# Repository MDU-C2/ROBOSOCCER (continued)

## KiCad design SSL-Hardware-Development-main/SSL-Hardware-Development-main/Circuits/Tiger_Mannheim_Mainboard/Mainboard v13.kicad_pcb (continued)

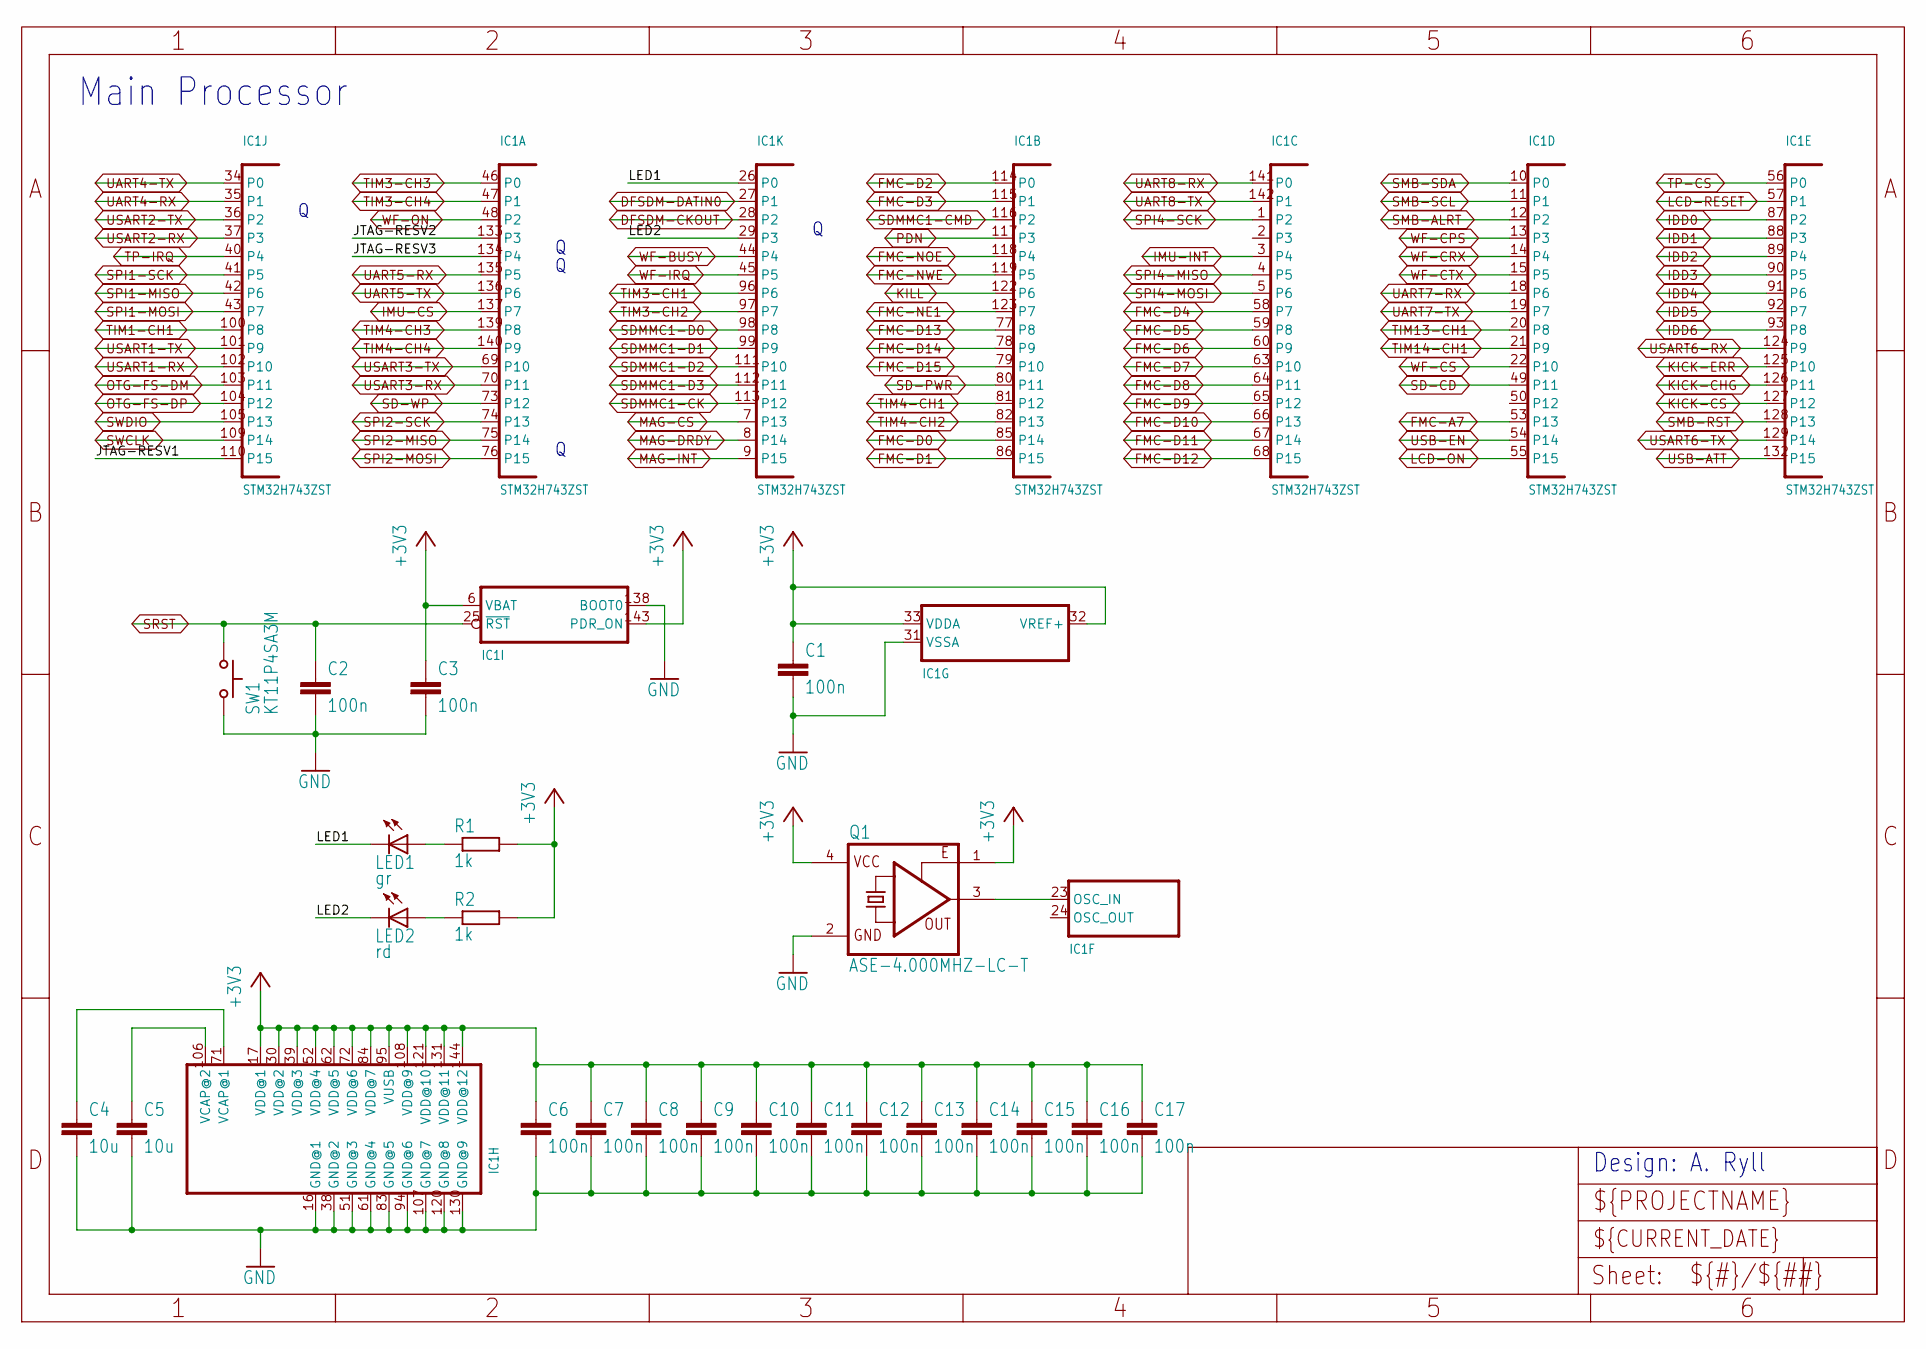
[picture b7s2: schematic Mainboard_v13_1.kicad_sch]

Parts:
C1, C2, C3, C6, C7, C8, C9, C10, C11, C12, C13, C14, C15, C16, C17: 100n; C0603
C4, C5: 10u; C0603
IC1: STM32H743ZST; LQFP144-ST
LED1: gr; CHIP-LED0603
LED2: rd; CHIP-LED0603
Q1: ASE-4.000MHZ-LC-T; OSCI-ASE
R1, R2: 1k; R0603
SW1: KT11P4SA3M; BUTTON4

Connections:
+3V3: C1.1, C3.1, C6.1, C7.1, C8.1, C9.1, C10.1, C11.1, C12.1, C13.1, C14.1, C15.1, C16.1, C17.1, IC1.6 (VBAT), IC1.17 (VDD@1), IC1.30 (VDD@2), IC1.32 (VREF+), IC1.33 (VDDA), IC1.39 (VDD@3), IC1.52 (VDD@4), IC1.62 (VDD@5), IC1.72 (VDD@6), IC1.84 (VDD@7), IC1.95 (VUSB), IC1.108 (VDD@9), IC1.121 (VDD@10), IC1.131 (VDD@11), IC1.143 (PDR_ON), IC1.144 (VDD@12), Q1.1 (OE), Q1.4 (VCC), R1.2, R2.2; also elsewhere on the board
DFSDM-CKOUT: IC1.28 (P2); also elsewhere on the board
DFSDM-DATIN0: IC1.27 (P1); also elsewhere on the board
FMC-A7: IC1.53 (P13); also elsewhere on the board
FMC-D0: IC1.85 (P14); also elsewhere on the board
FMC-D1: IC1.86 (P15); also elsewhere on the board
FMC-D2: IC1.114 (P0); also elsewhere on the board
FMC-D3: IC1.115 (P1); also elsewhere on the board
FMC-D4: IC1.58 (P7); also elsewhere on the board
FMC-D5: IC1.59 (P8); also elsewhere on the board
FMC-D6: IC1.60 (P9); also elsewhere on the board
FMC-D7: IC1.63 (P10); also elsewhere on the board
FMC-D8: IC1.64 (P11); also elsewhere on the board
FMC-D9: IC1.65 (P12); also elsewhere on the board
FMC-D10: IC1.66 (P13); also elsewhere on the board
FMC-D11: IC1.67 (P14); also elsewhere on the board
FMC-D12: IC1.68 (P15); also elsewhere on the board
FMC-D13: IC1.77 (P8); also elsewhere on the board
FMC-D14: IC1.78 (P9); also elsewhere on the board
FMC-D15: IC1.79 (P10); also elsewhere on the board
FMC-NE1: IC1.123 (P7); also elsewhere on the board
FMC-NOE: IC1.118 (P4); also elsewhere on the board
FMC-NWE: IC1.119 (P5); also elsewhere on the board
GND: C1.2, C2.2, C3.2, C4.2, C5.2, C6.2, C7.2, C8.2, C9.2, C10.2, C11.2, C12.2, C13.2, C14.2, C15.2, C16.2, C17.2, IC1.16 (GND@1), IC1.31 (VSSA), IC1.38 (GND@2), IC1.51 (GND@3), IC1.61 (GND@4), IC1.83 (GND@5), IC1.94 (GND@6), IC1.107 (GND@7), IC1.120 (GND@8), IC1.130 (GND@9), IC1.138 (BOOT0), Q1.2 (GND), SW1.3 (2), SW1.4 (2); also elsewhere on the board
IDD0: IC1.87 (P2); also elsewhere on the board
IDD1: IC1.88 (P3); also elsewhere on the board
IDD2: IC1.89 (P4); also elsewhere on the board
IDD3: IC1.90 (P5); also elsewhere on the board
IDD4: IC1.91 (P6); also elsewhere on the board
IDD5: IC1.92 (P7); also elsewhere on the board
IDD6: IC1.93 (P8); also elsewhere on the board
IMU-CS: IC1.137 (P7); also elsewhere on the board
IMU-INT: IC1.3 (P4); also elsewhere on the board
JTAG-RESV1: IC1.110 (P15)
JTAG-RESV2: IC1.133 (P3)
JTAG-RESV3: IC1.134 (P4)
KICK-CHG: IC1.126 (P11); also elsewhere on the board
KICK-CS: IC1.127 (P12); also elsewhere on the board
KICK-ERR: IC1.125 (P10); also elsewhere on the board
KILL: IC1.122 (P6); also elsewhere on the board
LCD-ON: IC1.55 (P15); also elsewhere on the board
LCD-RESET: IC1.57 (P1); also elsewhere on the board
LED1: IC1.26 (P0), LED1.C
LED2: IC1.29 (P3), LED2.C
MAG-CS: IC1.7 (P13); also elsewhere on the board
MAG-DRDY: IC1.8 (P14); also elsewhere on the board
MAG-INT: IC1.9 (P15); also elsewhere on the board
unnamed: LED1.A, R1.1
unnamed: LED2.A, R2.1
unnamed: IC1.23 (OSC_IN), Q1.3 (FO)
unnamed: C5.1, IC1.106 (VCAP@2)
unnamed: C4.1, IC1.71 (VCAP@1)
OTG-FS-DM: IC1.103 (P11); also elsewhere on the board
OTG-FS-DP: IC1.104 (P12); also elsewhere on the board
PDN: IC1.117 (P3); also elsewhere on the board
SD-CD: IC1.49 (P11); also elsewhere on the board
SD-PWR: IC1.80 (P11); also elsewhere on the board
SD-WP: IC1.73 (P12); also elsewhere on the board
SDMMC1-CK: IC1.113 (P12); also elsewhere on the board
SDMMC1-CMD: IC1.116 (P2); also elsewhere on the board
SDMMC1-D0: IC1.98 (P8); also elsewhere on the board
SDMMC1-D1: IC1.99 (P9); also elsewhere on the board
SDMMC1-D2: IC1.111 (P10); also elsewhere on the board
SDMMC1-D3: IC1.112 (P11); also elsewhere on the board
SMB-ALRT: IC1.12 (P2); also elsewhere on the board
SMB-RST: IC1.128 (P13); also elsewhere on the board
SMB-SCL: IC1.11 (P1); also elsewhere on the board
SMB-SDA: IC1.10 (P0); also elsewhere on the board
SPI1-MISO: IC1.42 (P6); also elsewhere on the board
SPI1-MOSI: IC1.43 (P7); also elsewhere on the board
SPI1-SCK: IC1.41 (P5); also elsewhere on the board
SPI2-MISO: IC1.75 (P14); also elsewhere on the board
SPI2-MOSI: IC1.76 (P15); also elsewhere on the board
SPI2-SCK: IC1.74 (P13); also elsewhere on the board
SPI4-MISO: IC1.4 (P5); also elsewhere on the board
SPI4-MOSI: IC1.5 (P6); also elsewhere on the board
SPI4-SCK: IC1.1 (P2); also elsewhere on the board
SRST: C2.1, IC1.25 (~RST), SW1.1, SW1.2 (1); also elsewhere on the board
SWCLK: IC1.109 (P14); also elsewhere on the board
SWDIO: IC1.105 (P13); also elsewhere on the board
TIM1-CH1: IC1.100 (P8); also elsewhere on the board
TIM3-CH1: IC1.96 (P6); also elsewhere on the board
TIM3-CH2: IC1.97 (P7); also elsewhere on the board
TIM3-CH3: IC1.46 (P0); also elsewhere on the board
TIM3-CH4: IC1.47 (P1); also elsewhere on the board
TIM4-CH1: IC1.81 (P12); also elsewhere on the board
TIM4-CH2: IC1.82 (P13); also elsewhere on the board
TIM4-CH3: IC1.139 (P8); also elsewhere on the board
TIM4-CH4: IC1.140 (P9); also elsewhere on the board
TIM13-CH1: IC1.20 (P8); also elsewhere on the board
TIM14-CH1: IC1.21 (P9); also elsewhere on the board
TP-CS: IC1.56 (P0); also elsewhere on the board
TP-IRQ: IC1.40 (P4); also elsewhere on the board
UART4-RX: IC1.35 (P1); also elsewhere on the board
UART4-TX: IC1.34 (P0); also elsewhere on the board
UART5-RX: IC1.135 (P5); also elsewhere on the board
UART5-TX: IC1.136 (P6); also elsewhere on the board
UART7-RX: IC1.18 (P6); also elsewhere on the board
UART7-TX: IC1.19 (P7); also elsewhere on the board
UART8-RX: IC1.141 (P0); also elsewhere on the board
UART8-TX: IC1.142 (P1); also elsewhere on the board
USART1-RX: IC1.102 (P10); also elsewhere on the board
USART1-TX: IC1.101 (P9); also elsewhere on the board
USART2-RX: IC1.37 (P3); also elsewhere on the board
USART2-TX: IC1.36 (P2); also elsewhere on the board
USART3-RX: IC1.70 (P11); also elsewhere on the board
USART3-TX: IC1.69 (P10); also elsewhere on the board
USART6-RX: IC1.124 (P9); also elsewhere on the board
USART6-TX: IC1.129 (P14); also elsewhere on the board
USB-ATT: IC1.132 (P15); also elsewhere on the board
USB-EN: IC1.54 (P14); also elsewhere on the board
WF-BUSY: IC1.44 (P4); also elsewhere on the board
WF-CPS: IC1.13 (P3); also elsewhere on the board
WF-CRX: IC1.14 (P4); also elsewhere on the board
WF-CS: IC1.22 (P10); also elsewhere on the board
WF-CTX: IC1.15 (P5); also elsewhere on the board
WF-IRQ: IC1.45 (P5); also elsewhere on the board
WF-ON: IC1.48 (P2); also elsewhere on the board

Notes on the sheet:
Main Processor
Design: A. Ryll

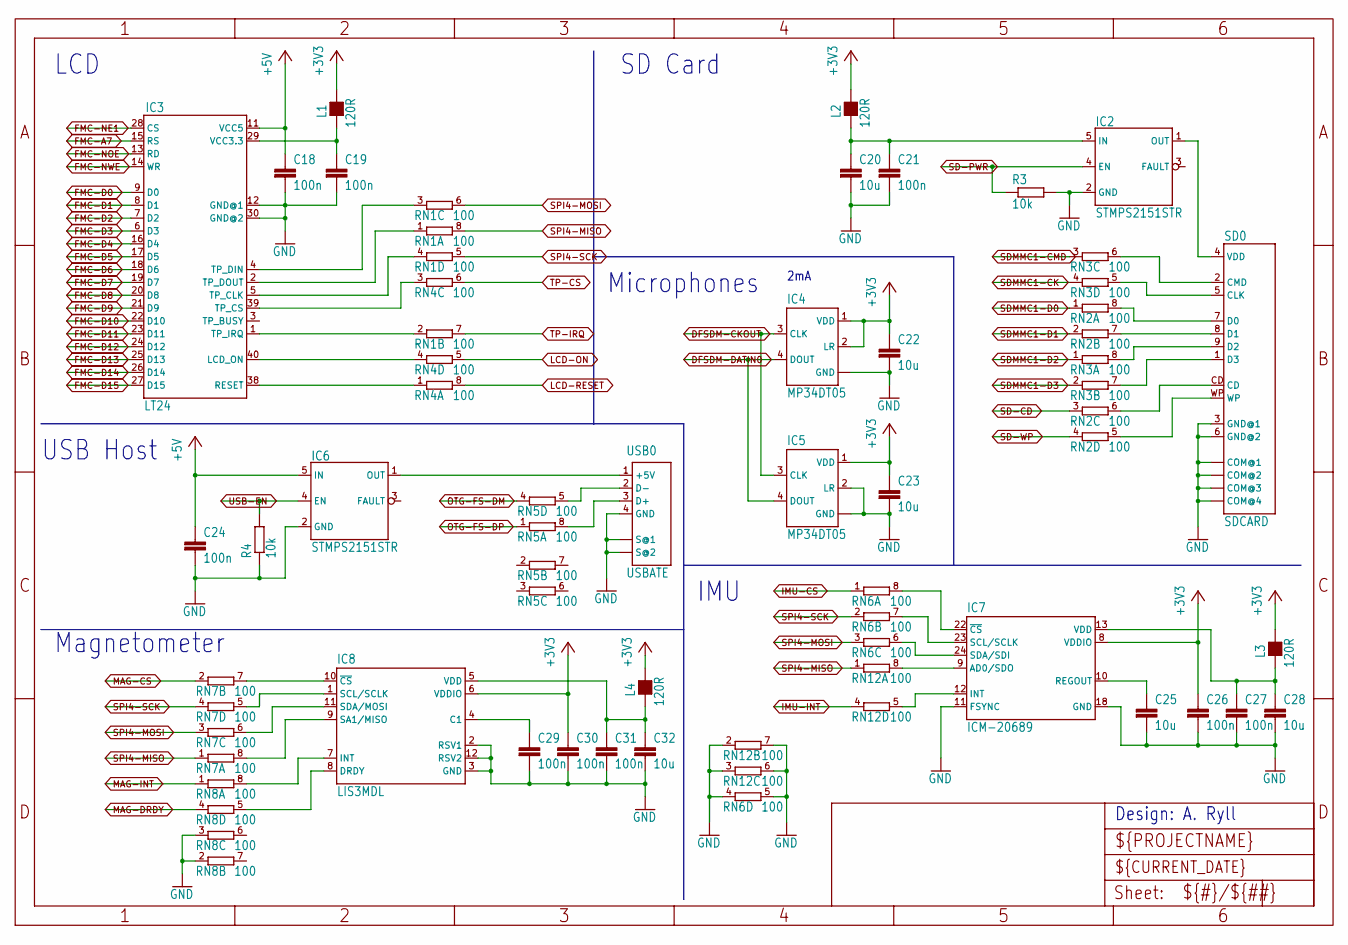
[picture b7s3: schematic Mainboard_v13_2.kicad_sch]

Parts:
C18, C19, C21, C24, C26, C27, C29, C30, C31: 100n; C0603
C20, C22, C23, C25, C28, C32: 10u; C0603
IC2, IC6: STMPS2151STR; SOT23-5
IC3: LT24
IC4, IC5: MP34DT05; HCLGA4
IC7: ICM-20689; QFN24-4X4-P
IC8: LIS3MDL; VFLGA-12
L1, L2, L3, L4: 120R; L0603
R3, R4: 10k; R0603
RN1, RN2, RN3, RN4, RN5, RN6, RN7, RN8, RN12: 100; EXB28V
SD0: SDCARD
USB0: USBATE; USBA-TE

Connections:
+3V3: C22.1, C23.1, C26.1, C30.1, IC4.1 (VDD), IC4.2 (LR), IC5.1 (VDD), IC7.8 (VDDIO), IC8.6 (VDDIO), L1.2, L2.2, L3.2, L4.2; also elsewhere on the board
+5V: C18.1, C24.1, IC3.11 (VCC5), IC6.5 (IN); also elsewhere on the board
DFSDM-CKOUT: IC4.3 (CLK), IC5.3 (CLK); also elsewhere on the board
DFSDM-DATIN0: IC4.4 (DOUT), IC5.4 (DOUT); also elsewhere on the board
FMC-A7: IC3.15 (RS); also elsewhere on the board
FMC-D0: IC3.9 (D0); also elsewhere on the board
FMC-D1: IC3.8 (D1); also elsewhere on the board
FMC-D2: IC3.7 (D2); also elsewhere on the board
FMC-D3: IC3.6 (D3); also elsewhere on the board
FMC-D4: IC3.16 (D4); also elsewhere on the board
FMC-D5: IC3.17 (D5); also elsewhere on the board
FMC-D6: IC3.18 (D6); also elsewhere on the board
FMC-D7: IC3.19 (D7); also elsewhere on the board
FMC-D8: IC3.20 (D8); also elsewhere on the board
FMC-D9: IC3.21 (D9); also elsewhere on the board
FMC-D10: IC3.22 (D10); also elsewhere on the board
FMC-D11: IC3.23 (D11); also elsewhere on the board
FMC-D12: IC3.24 (D12); also elsewhere on the board
FMC-D13: IC3.25 (D13); also elsewhere on the board
FMC-D14: IC3.26 (D14); also elsewhere on the board
FMC-D15: IC3.27 (D15); also elsewhere on the board
FMC-NE1: IC3.28 (CS); also elsewhere on the board
FMC-NOE: IC3.13 (RD); also elsewhere on the board
FMC-NWE: IC3.14 (WR); also elsewhere on the board
GND: C18.2, C19.2, C20.2, C21.2, C22.2, C23.2, C24.2, C25.2, C26.2, C27.2, C28.2, C29.2, C30.2, C31.2, C32.2, IC2.2 (GND), IC3.12 (GND@1), IC3.30 (GND@2), IC4.G1 (GND), IC4.G2 (GND), IC4.G3 (GND), IC4.G4 (GND), IC5.2 (LR), IC5.G1 (GND), IC5.G2 (GND), IC5.G3 (GND), IC5.G4 (GND), IC6.2 (GND), IC7.11 (FSYNC), IC7.18 (GND), IC8.2 (RSV1), IC8.3 (GND), IC8.12 (RSV2), R3.2, R4.1, RN6.4 (1), RN6.5 (2), RN8.2 (1), RN8.3 (1), RN12.2 (1), RN12.3 (1), RN12.6 (2), RN12.7 (2), SD0.3 (GND@1), SD0.6 (GND@2), SD0.COM1 (COM@1), SD0.COM2 (COM@2), SD0.COM3 (COM@3), SD0.COM4 (COM@4), USB0.4 (GND), USB0.MNT1 (S@1), USB0.MNT2 (S@2); also elsewhere on the board
IMU-CS: RN6.1; also elsewhere on the board
IMU-INT: RN12.4 (1); also elsewhere on the board
LCD-ON: RN4.5 (2); also elsewhere on the board
LCD-RESET: RN4.8 (2); also elsewhere on the board
MAG-CS: RN7.2 (1); also elsewhere on the board
MAG-DRDY: RN8.4 (1); also elsewhere on the board
MAG-INT: RN8.1; also elsewhere on the board
unnamed: IC8.10 (~CS), RN7.7 (2)
unnamed: IC8.1 (SCL/SCLK), RN7.5 (2)
unnamed: IC8.11 (SDA/MOSI), RN7.6 (2)
unnamed: IC8.9 (SA1/MISO), RN7.8 (2)
unnamed: IC8.7 (INT), RN8.8 (2)
unnamed: IC8.8 (DRDY), RN8.5 (2)
unnamed: C29.1, IC8.4 (C1)
unnamed: C31.1, C32.1, IC8.5 (VDD), L4.1
unnamed: IC7.12 (INT), RN12.5 (2)
unnamed: C19.1, IC3.29 (VCC3.3), L1.1
unnamed: IC3.38 (RESET), RN4.1
unnamed: IC3.40 (LCD_ON), RN4.4 (1)
unnamed: IC3.1 (TP_IRQ), RN1.2 (1)
unnamed: IC3.39 (TP_CS), RN4.3 (1)
unnamed: IC3.5 (TP_CLK), RN1.4 (1)
unnamed: IC3.2 (TP_DOUT), RN1.1
unnamed: IC3.4 (TP_DIN), RN1.3 (1)
unnamed: RN2.7 (2), SD0.8 (D1)
unnamed: RN2.8 (2), SD0.7 (D0)
unnamed: RN3.5 (2), SD0.5 (CLK)
unnamed: RN3.6 (2), SD0.2 (CMD)
unnamed: RN3.8 (2), SD0.9 (D2)
unnamed: RN3.7 (2), SD0.1 (D3)
unnamed: RN2.6 (2), SD0.CD
unnamed: RN2.5 (2), SD0.WP
unnamed: C20.1, C21.1, IC2.5 (IN), L2.1
unnamed: IC6.1 (OUT), USB0.1 (+5V)
unnamed: RN5.5 (2), USB0.2 (D-)
unnamed: RN5.8 (2), USB0.3 (D+)
unnamed: IC7.9 (AD0/SDO), RN12.8 (2)
unnamed: C25.1, IC7.10 (REGOUT)
unnamed: C27.1, C28.1, IC7.13 (VDD), L3.1
unnamed: IC7.24 (SDA/SDI), RN6.6 (2)
unnamed: IC7.23 (SCL/SCLK), RN6.7 (2)
unnamed: IC7.22 (~CS), RN6.8 (2)
OTG-FS-DM: RN5.4 (1); also elsewhere on the board
OTG-FS-DP: RN5.1; also elsewhere on the board
SD-CD: RN2.3 (1); also elsewhere on the board
SD-PWR: IC2.4 (EN), R3.1; also elsewhere on the board
SD-WP: RN2.4 (1); also elsewhere on the board
SDMMC1-CK: RN3.4 (1); also elsewhere on the board
SDMMC1-CMD: RN3.3 (1); also elsewhere on the board
SDMMC1-D0: RN2.1; also elsewhere on the board
SDMMC1-D1: RN2.2 (1); also elsewhere on the board
SDMMC1-D2: RN3.1; also elsewhere on the board
SDMMC1-D3: RN3.2 (1); also elsewhere on the board
SD_PWR: IC2.1 (OUT), SD0.4 (VDD)
SPI4-MISO: RN1.8 (2), RN7.1, RN12.1; also elsewhere on the board
SPI4-MOSI: RN1.6 (2), RN6.3 (1), RN7.3 (1); also elsewhere on the board
SPI4-SCK: RN1.5 (2), RN6.2 (1), RN7.4 (1); also elsewhere on the board
TP-CS: RN4.6 (2); also elsewhere on the board
TP-IRQ: RN1.7 (2); also elsewhere on the board
USB-EN: IC6.4 (EN), R4.2; also elsewhere on the board

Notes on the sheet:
2mA
IMU
Design: A. Ryll
USB Host
SD Card
Magnetometer
Microphones
LCD

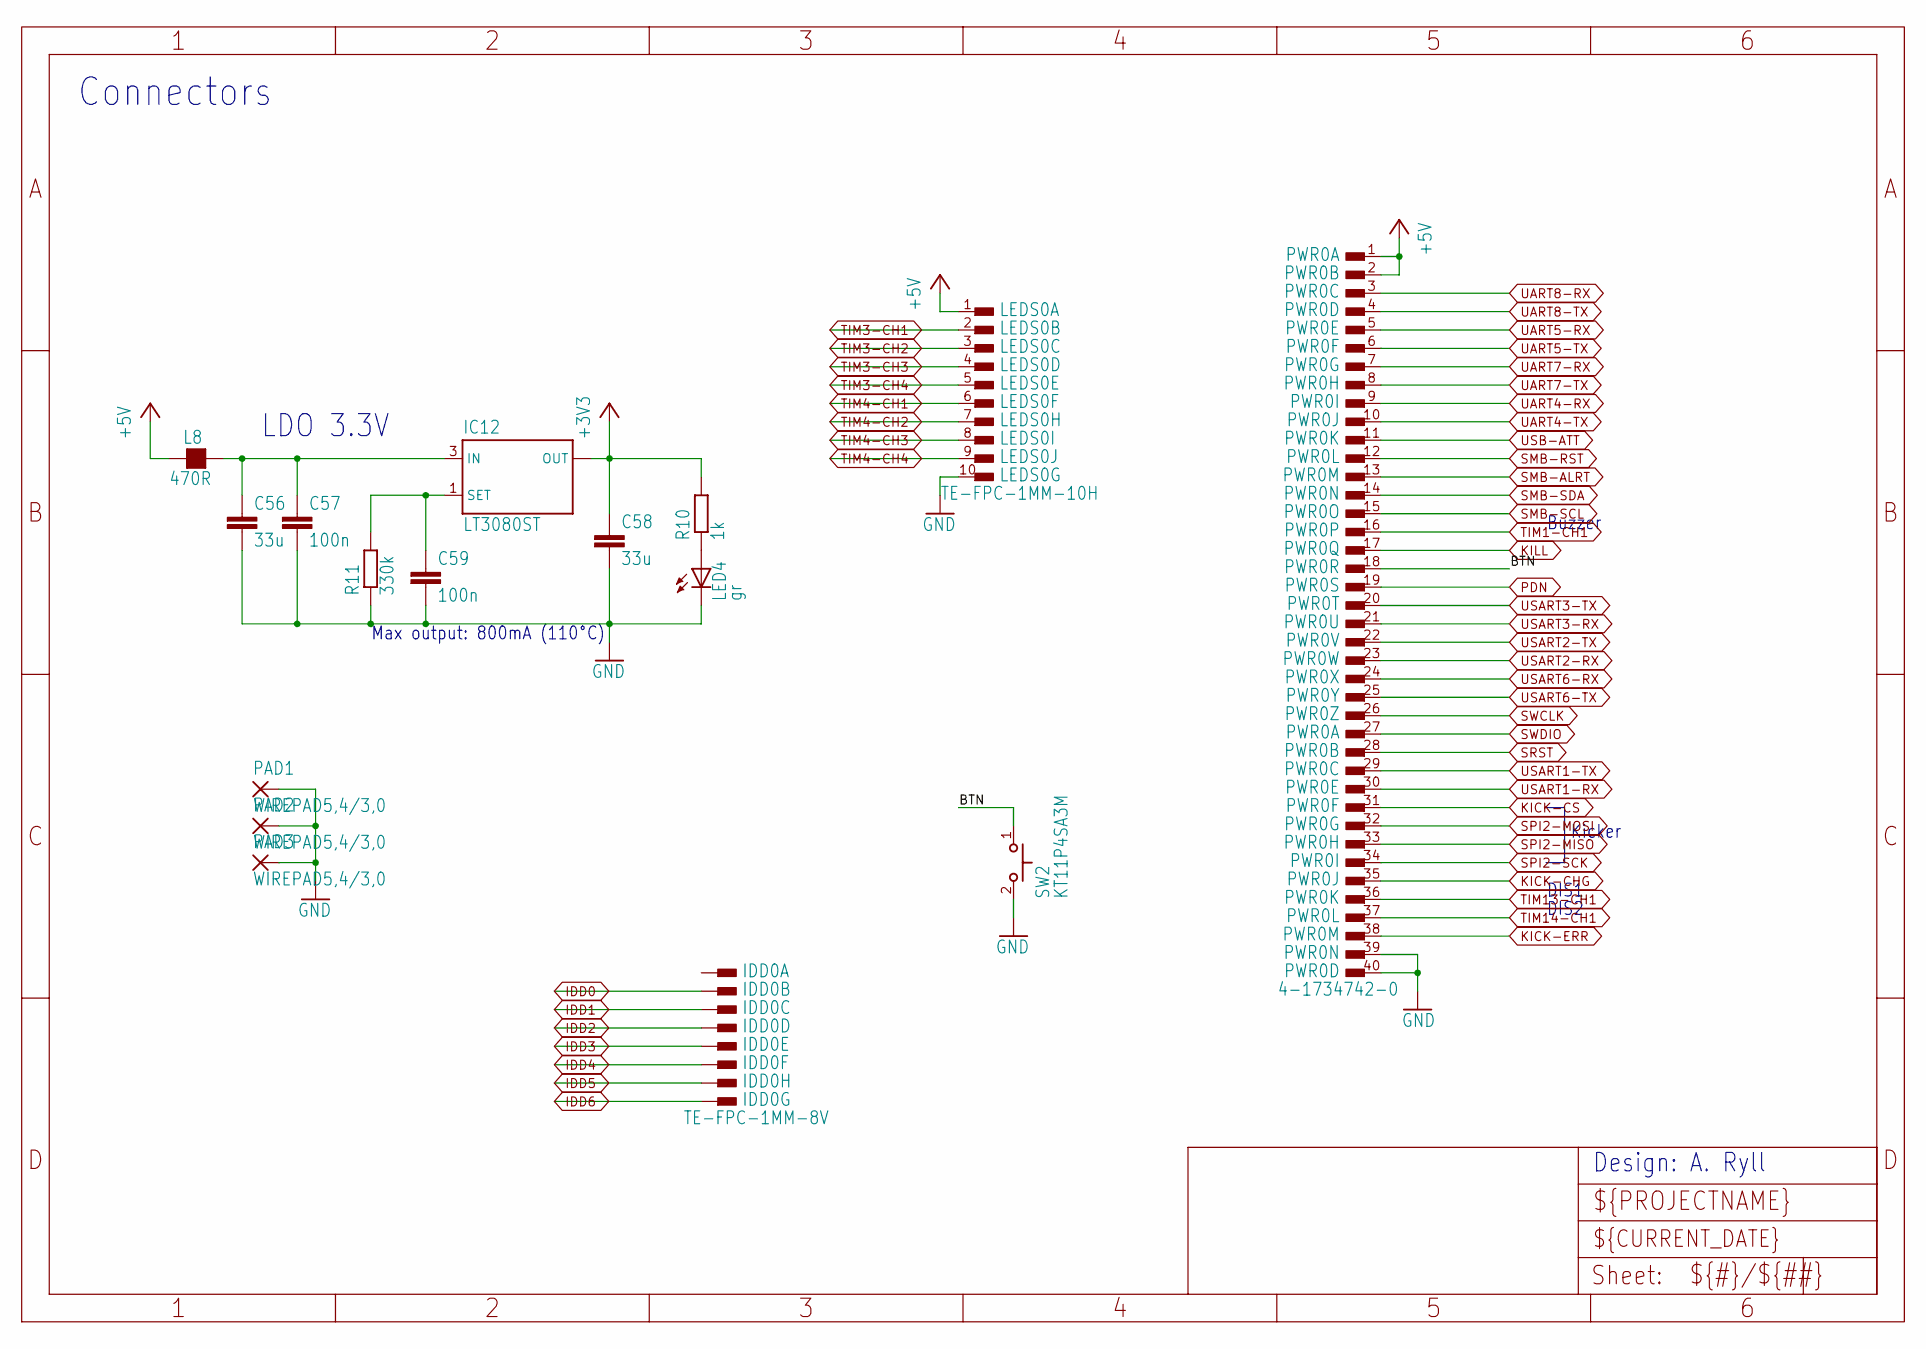
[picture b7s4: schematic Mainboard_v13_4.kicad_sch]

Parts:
C56, C58: 33u; C1206; VOLTAGE 25V
C57, C59: 100n; C0603
IC12: LT3080ST; SOT223
IDD0: TE-FPC-1MM-8V; TE-1734248-8
L8: 470R; L1206
LED4: gr; CHIP-LED0603
LEDS0: TE-FPC-1MM-10H; TE-1-84952-0
PAD1, PAD2, PAD3: WIREPAD5,4/3,0; 5,4_3,0
PWR0: 4-1734742-0; TE-4-1734592-0
R10: 1k; R0603
R11: 330k; R0603
SW2: KT11P4SA3M; KT11

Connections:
+3V3: C58.1, IC12.2 (OUT), IC12.4 (OUT), R10.2; also elsewhere on the board
+5V: L8.1, LEDS0.1, PWR0.1, PWR0.2; also elsewhere on the board
BTN: PWR0.18, SW2.1
GND: C56.2, C57.2, C58.2, C59.2, LED4.C, LEDS0.10, PAD1.1, PAD1.2, PAD2.1, PAD2.2, PAD3.1, PAD3.2, PWR0.39, PWR0.40, R11.1, SW2.2; also elsewhere on the board
IDD0: IDD0.A2, IDD0.B2; also elsewhere on the board
IDD1: IDD0.A3, IDD0.B3; also elsewhere on the board
IDD2: IDD0.A4, IDD0.B4; also elsewhere on the board
IDD3: IDD0.A5, IDD0.B5; also elsewhere on the board
IDD4: IDD0.A6, IDD0.B6; also elsewhere on the board
IDD5: IDD0.A7, IDD0.B7; also elsewhere on the board
IDD6: IDD0.A8, IDD0.B8; also elsewhere on the board
KICK-CHG: PWR0.35; also elsewhere on the board
KICK-CS: PWR0.31; also elsewhere on the board
KICK-ERR: PWR0.38; also elsewhere on the board
KILL: PWR0.17; also elsewhere on the board
unnamed: C59.1, IC12.1 (SET), R11.2
unnamed: LED4.A, R10.1
unnamed: C56.1, C57.1, IC12.3 (IN), L8.2
PDN: PWR0.19; also elsewhere on the board
SMB-ALRT: PWR0.13; also elsewhere on the board
SMB-RST: PWR0.12; also elsewhere on the board
SMB-SCL: PWR0.15; also elsewhere on the board
SMB-SDA: PWR0.14; also elsewhere on the board
SPI2-MISO: PWR0.33; also elsewhere on the board
SPI2-MOSI: PWR0.32; also elsewhere on the board
SPI2-SCK: PWR0.34; also elsewhere on the board
SRST: PWR0.28; also elsewhere on the board
SWCLK: PWR0.26; also elsewhere on the board
SWDIO: PWR0.27; also elsewhere on the board
TIM1-CH1: PWR0.16; also elsewhere on the board
TIM3-CH1: LEDS0.2; also elsewhere on the board
TIM3-CH2: LEDS0.3; also elsewhere on the board
TIM3-CH3: LEDS0.4; also elsewhere on the board
TIM3-CH4: LEDS0.5; also elsewhere on the board
TIM4-CH1: LEDS0.6; also elsewhere on the board
TIM4-CH2: LEDS0.7; also elsewhere on the board
TIM4-CH3: LEDS0.8; also elsewhere on the board
TIM4-CH4: LEDS0.9; also elsewhere on the board
TIM13-CH1: PWR0.36; also elsewhere on the board
TIM14-CH1: PWR0.37; also elsewhere on the board
UART4-RX: PWR0.9; also elsewhere on the board
UART4-TX: PWR0.10; also elsewhere on the board
UART5-RX: PWR0.5; also elsewhere on the board
UART5-TX: PWR0.6; also elsewhere on the board
UART7-RX: PWR0.7; also elsewhere on the board
UART7-TX: PWR0.8; also elsewhere on the board
UART8-RX: PWR0.3; also elsewhere on the board
UART8-TX: PWR0.4; also elsewhere on the board
USART1-RX: PWR0.30; also elsewhere on the board
USART1-TX: PWR0.29; also elsewhere on the board
USART2-RX: PWR0.23; also elsewhere on the board
USART2-TX: PWR0.22; also elsewhere on the board
USART3-RX: PWR0.21; also elsewhere on the board
USART3-TX: PWR0.20; also elsewhere on the board
USART6-RX: PWR0.24; also elsewhere on the board
USART6-TX: PWR0.25; also elsewhere on the board
USB-ATT: PWR0.11; also elsewhere on the board

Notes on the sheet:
Max output: 800mA (110°C)
LDO 3.3V
Connectors
Kicker
DIS1
DIS2
Design: A. Ryll
Buzzer

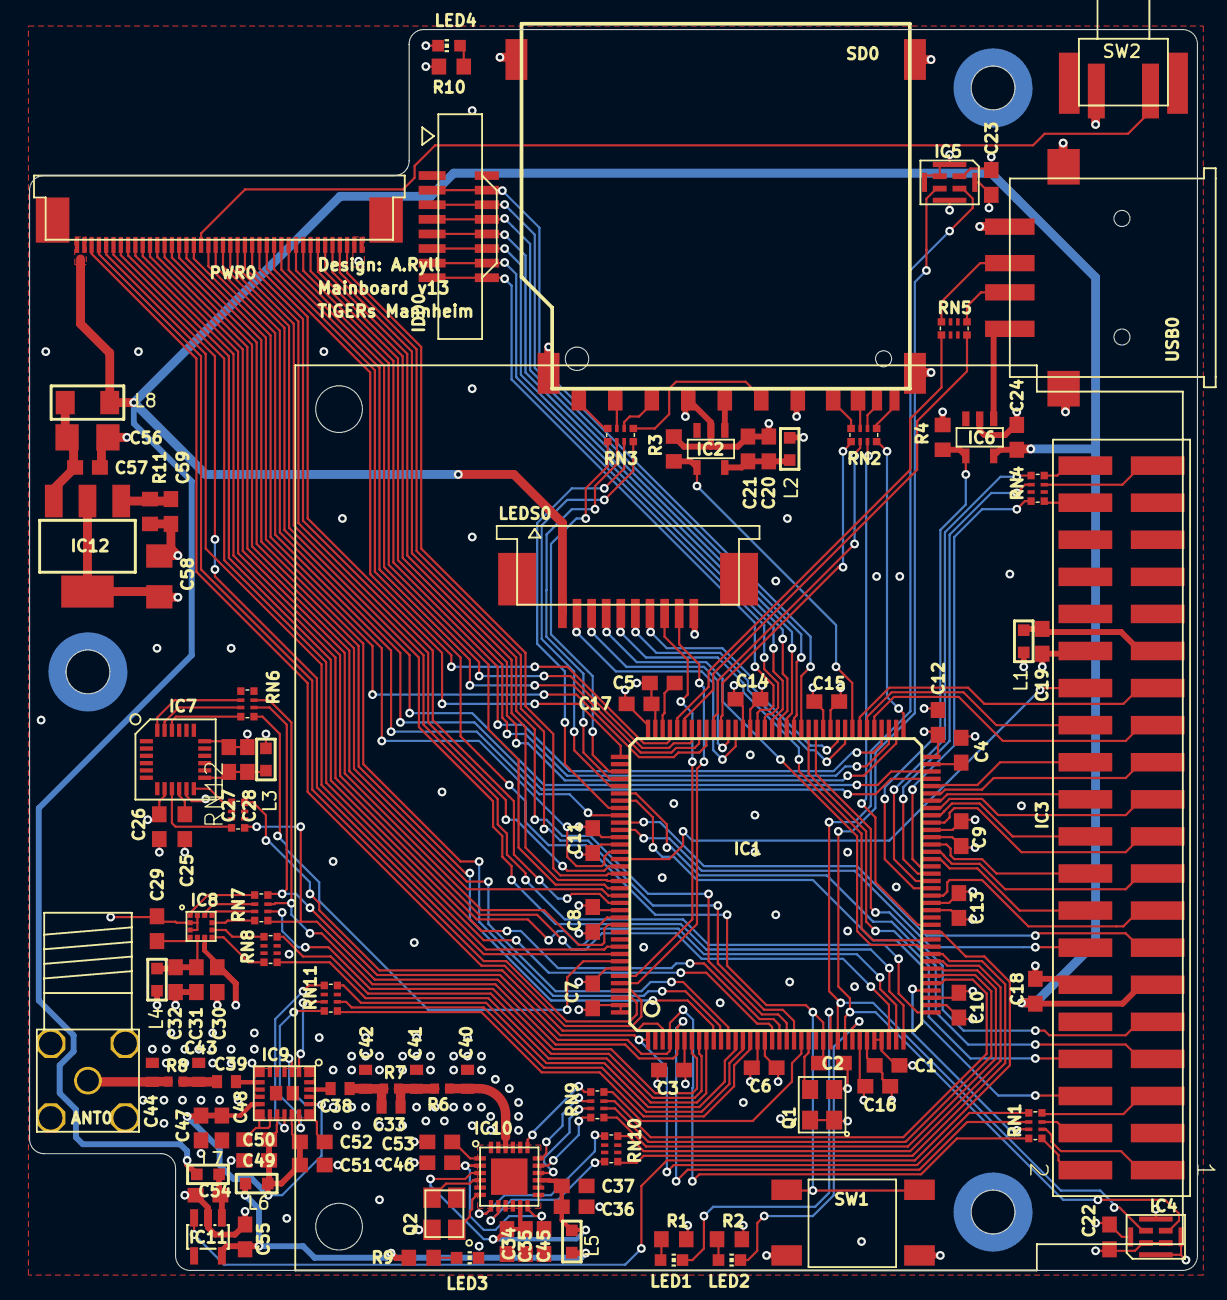
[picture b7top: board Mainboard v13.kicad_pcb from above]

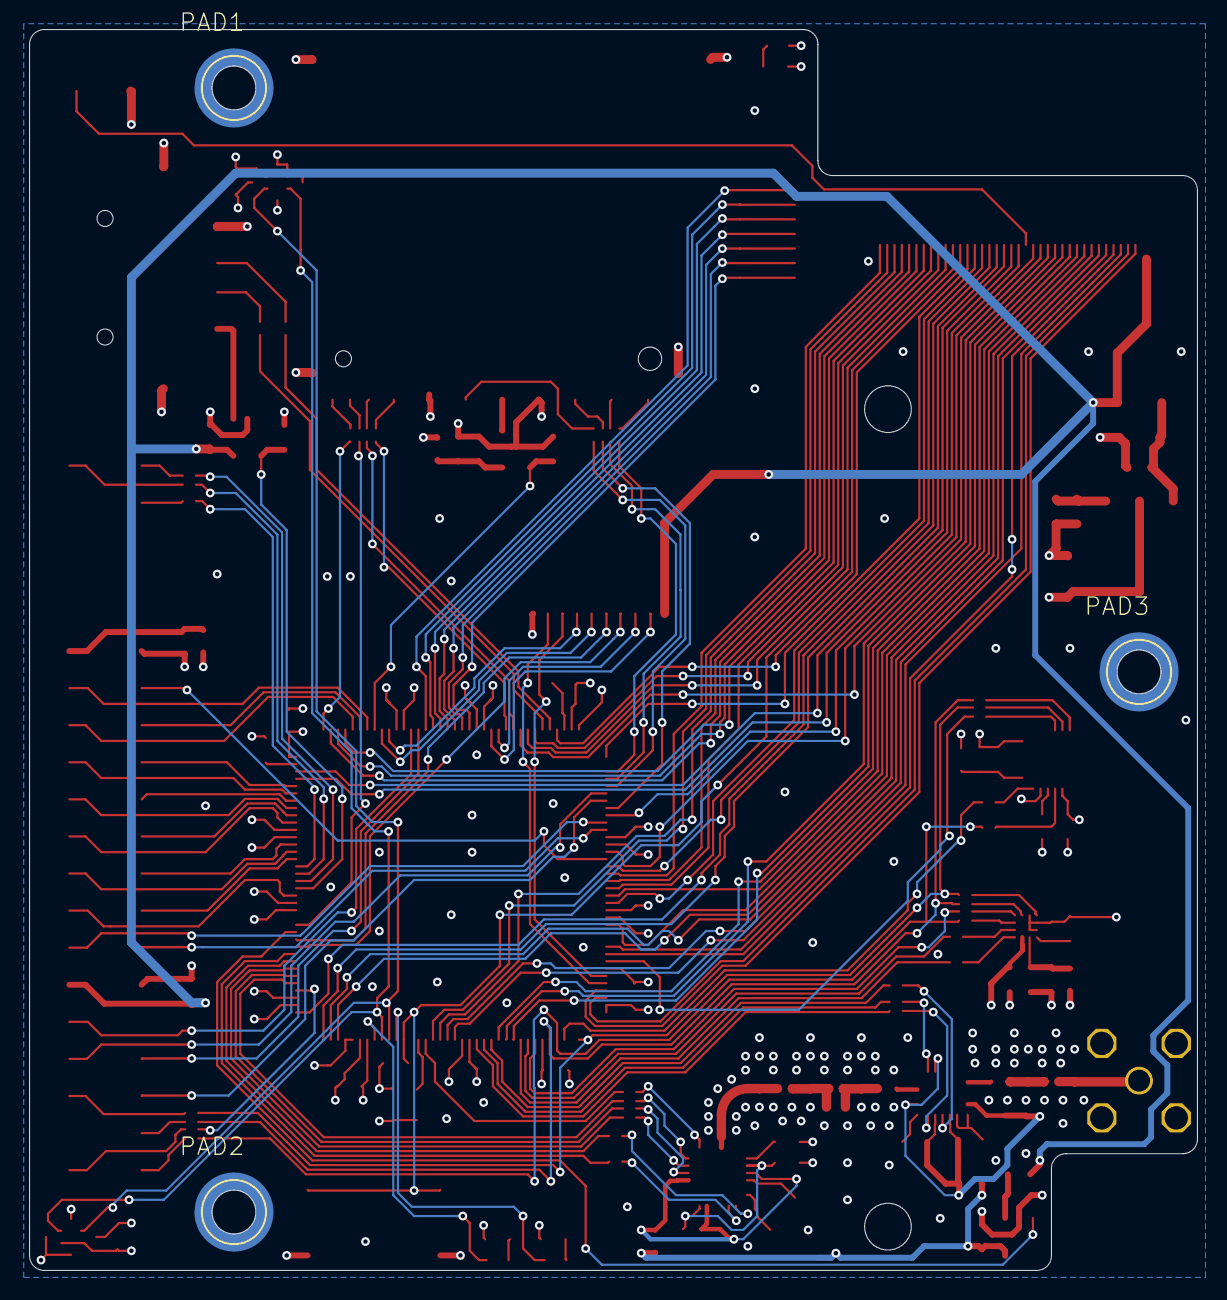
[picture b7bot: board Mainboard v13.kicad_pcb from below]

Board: 4 copper layers, 80.0 x 85.0 mm, 118 parts (3 on the bottom side), 181 nets.

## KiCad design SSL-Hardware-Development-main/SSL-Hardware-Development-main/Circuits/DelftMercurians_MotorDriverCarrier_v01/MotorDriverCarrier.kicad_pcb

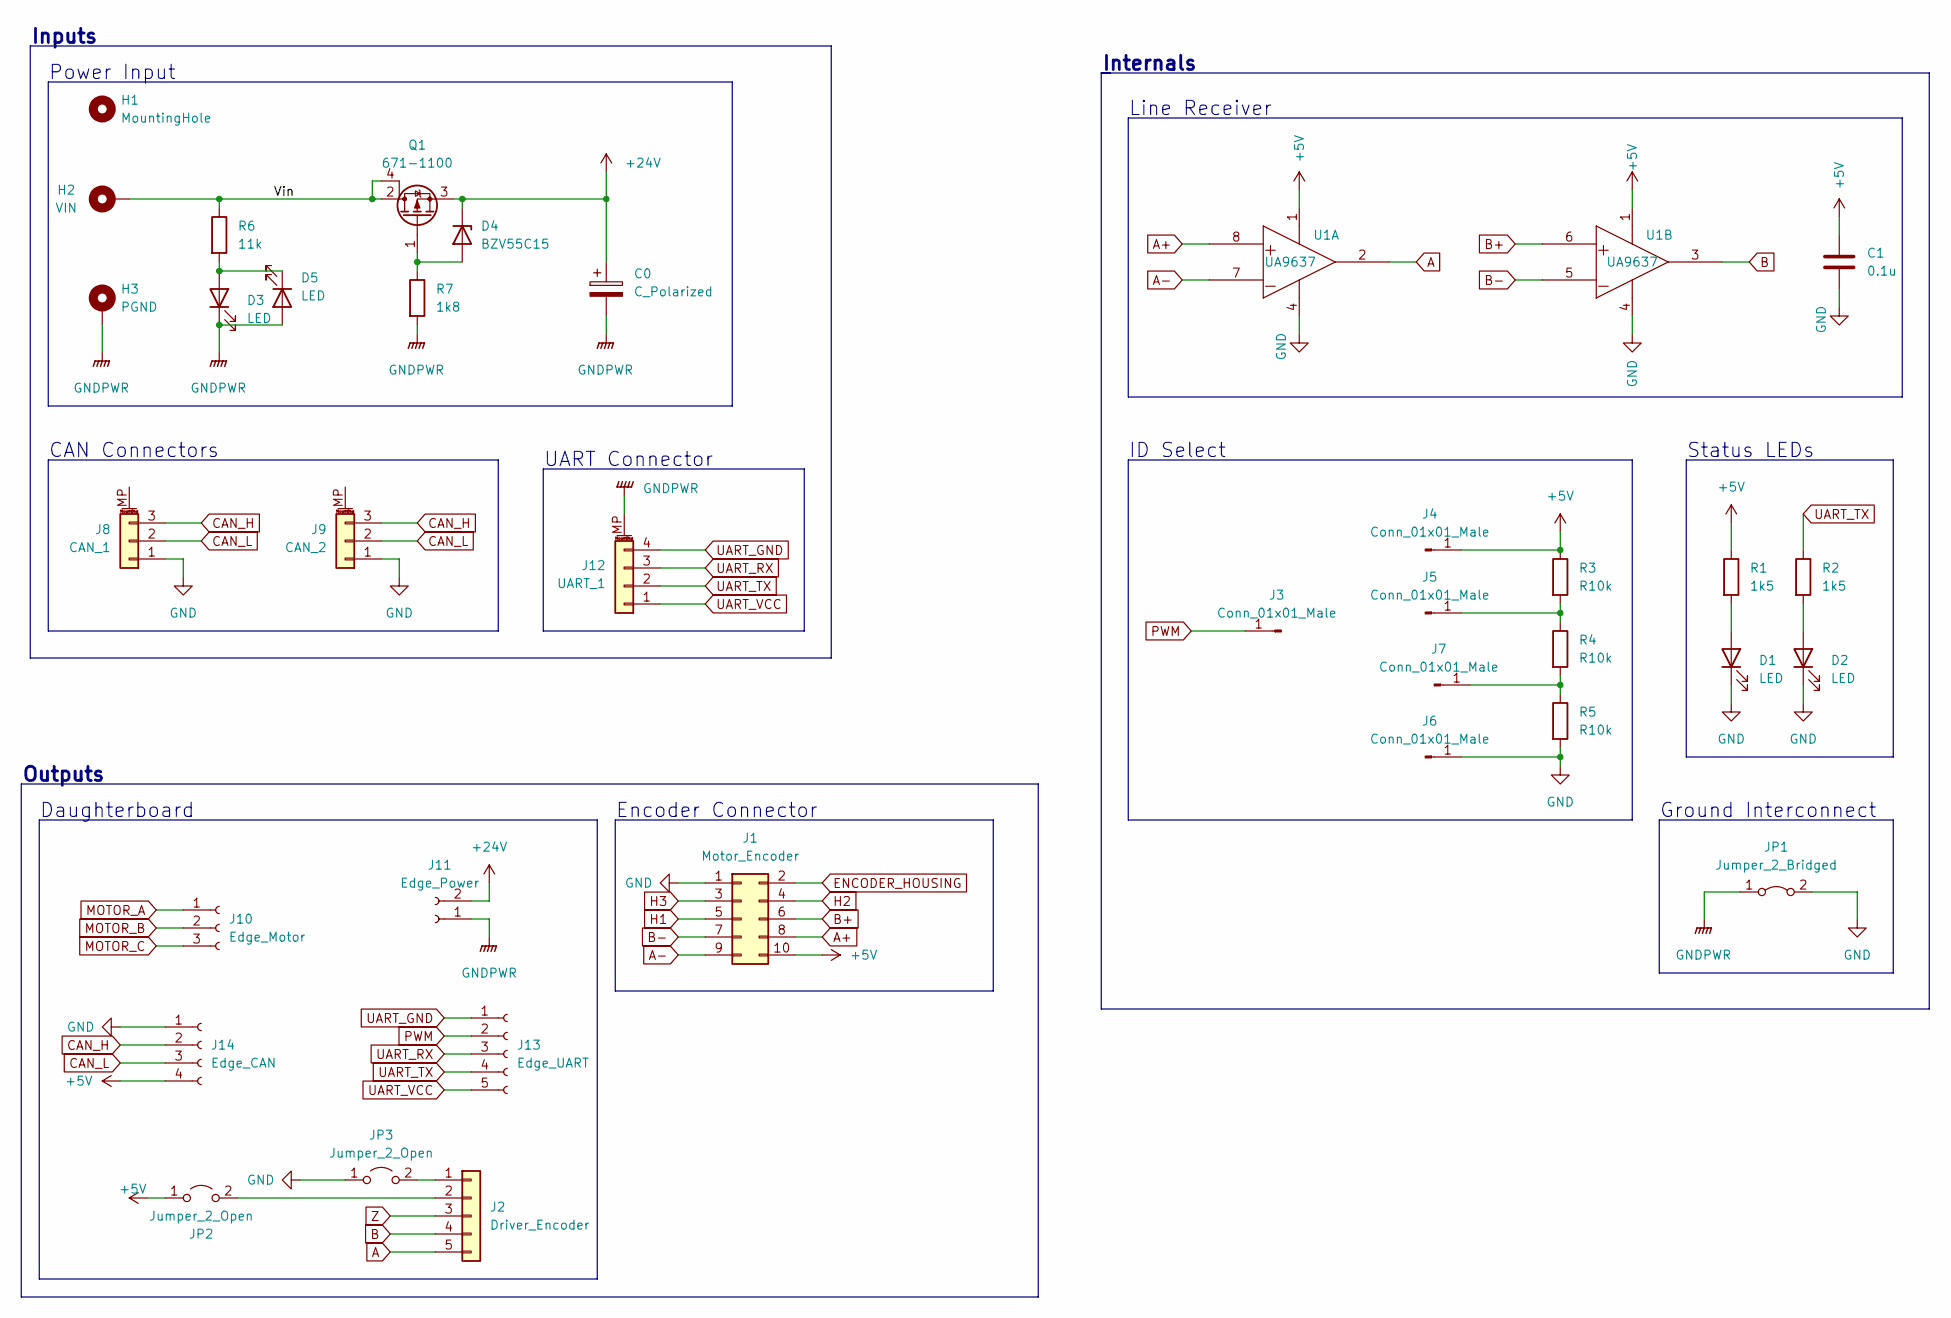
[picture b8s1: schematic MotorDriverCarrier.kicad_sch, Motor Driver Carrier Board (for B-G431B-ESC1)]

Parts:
C0: C_Polarized; CP_Radial_D8.0mm_P3.50mm
C1: 0.1u; C_0603_1608Metric_Pad1.08x0.95mm_HandSolder
D1, D2, D3, D5: LED; LED_0603_1608Metric_Pad1.05x0.95mm_HandSolder
D4: BZV55C15; D_MiniMELF
H1: MountingHole; MountingHole_3.2mm_M3_ISO14580
H2: VIN; MountingHole_3.2mm_M3_ISO7380_Pad_TopOnly
H3: PGND; MountingHole_3.2mm_M3_ISO7380_Pad_TopOnly
J1: Motor_Encoder; PinHeader_2x05_P1.27mm_Vertical
J2: Driver_Encoder; PinHeader_1x05_P1.27mm_Vertical
J3, J4, J5, J6, J7: Conn_01x01_Male; PinHeader_1x01_P2.54mm_Vertical
J8: CAN_1; JST_GH_SM03B-GHS-TB_1x03-1MP_P1.25mm_Horizontal
J9: CAN_2; JST_GH_SM03B-GHS-TB_1x03-1MP_P1.25mm_Horizontal
J10: Edge_Motor; CustomEdge_Motor3
J11: Edge_Power; CustomEdge_Power2
J12: UART_1; JST_GH_SM04B-GHS-TB_1x04-1MP_P1.25mm_Horizontal
J13: Edge_UART; CustomEdge_UART5
J14: Edge_CAN; CustomEdge_CAN4
JP1: Jumper_2_Bridged; SolderJumper-2_P1.3mm_Open_TrianglePad1.0x1.5mm
JP2, JP3: Jumper_2_Open; SolderJumper-2_P1.3mm_Open_RoundedPad1.0x1.5mm
Q1: 671-1100; SOT-223-3_TabPin2
R1, R2: 1k5; R_0603_1608Metric_Pad0.98x0.95mm_HandSolder
R3, R4, R5: R10k; R_0603_1608Metric_Pad0.98x0.95mm_HandSolder
R6: 11k; R_0603_1608Metric_Pad0.98x0.95mm_HandSolder
R7: 1k8; R_0603_1608Metric_Pad0.98x0.95mm_HandSolder
U1: UA9637; SOIC-8_3.9x4.9mm_P1.27mm

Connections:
+5V: C1.1, J1.10, J4.1, J14.4, JP2.1 (A), R1.1, R3.1, U1.1 (VCC)
+24V: C0.1, D4.1 (K), J11.2, Q1.3 (S)
/Vin: H2.1, Q1.2 (D), Q1.4 (D), R6.1
A: J2.5, U1.2 (OUT)
A+: J1.8, U1.8 (IN+)
A-: J1.9, U1.7 (IN-)
B: J2.4, U1.3 (OUT)
B+: J1.6, U1.6 (IN+)
B-: J1.7, U1.5 (IN-)
CAN_H: J8.3, J9.3, J14.2
CAN_L: J8.2, J9.2, J14.3
ENCODER_HOUSING: J1.2
GND: C1.2, D1.1 (K), D2.1 (K), J1.1, J6.1, J8.1, J9.1, J14.1, JP1.2 (B), JP3.1 (A), R5.2, U1.4 (GND)
GNDPWR: C0.2, D3.1 (K), D5.2 (A), H3.1, J11.1, J12.MP (MountPin), JP1.1 (A), R7.2
H1: J1.5
H2: J1.4
H3: J1.3
MOTOR_A: J10.1
MOTOR_B: J10.2
MOTOR_C: J10.3
unnamed: D1.2 (A), R1.2
unnamed: D2.2 (A), R2.2
unnamed: D3.2 (A), D5.1 (K), R6.2
unnamed: D4.2 (A), Q1.1 (G), R7.1
unnamed: J2.1, JP3.2 (B)
unnamed: J2.2, JP2.2 (B)
unnamed: J5.1, R3.2, R4.1
unnamed: J7.1, R4.2, R5.1
PWM: J3.1, J13.2
UART_GND: J12.4, J13.1
UART_RX: J12.3, J13.3
UART_TX: J12.2, J13.4, R2.1
UART_VCC: J12.1, J13.5
Z: J2.3

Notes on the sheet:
Daughterboard
CAN Connectors
ID Select
UART Connector
Internals
Encoder Connector
Status LEDs
Line Receiver
Ground Interconnect
Power Input
Outputs
Inputs
